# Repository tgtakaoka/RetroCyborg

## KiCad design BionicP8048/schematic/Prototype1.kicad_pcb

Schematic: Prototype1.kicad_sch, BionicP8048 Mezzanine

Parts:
C1: 0.1u; C_Disc_D3.4mm_W2.1mm_P2.50mm
J1: BionicConnector; DIP-48_W7.62mm
U1: MSM80C39RS; DIP-40_W15.24mm
U2: 74HCT126; DIP-14_W7.62mm

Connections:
/P10: J1.2 (P10), U1.12 (DB0)
/P11: J1.3 (P11), U1.13 (DB1)
/P12: J1.4 (P12), U1.14 (DB2)
/P13: J1.5 (P13), U1.15 (DB3)
/P14: J1.6 (P14), U1.16 (DB4)
/P15: J1.7 (P15), U1.17 (DB5)
/P16: J1.8 (P16), U1.18 (DB6)
/P17: J1.9 (P17), U1.19 (DB7)
/P20: J1.47 (P20), U1.21 (A8)
/P21: J1.46 (P21), U1.22 (A9)
/P22: J1.45 (P22), U1.23 (A10)
/P23: J1.44 (P23), U1.24 (A11)
/P40: J1.38 (P40), U1.11 (ALE)
/P41: J1.37 (P41), U1.9 (~PSEN)
/P42: J1.36 (P42), U1.6 (~INT)
/P44: J1.34 (P44), U1.1 (T0)
/P45: J1.33 (P45), U1.39 (T1)
/P46: J1.32 (P46), U2.2 (1A)
/P50: J1.20 (P50), U1.8 (~RD)
/P51: J1.21 (P51), U1.10 (~WR)
/P52: J1.22 (P52), U1.5 (~SS)
/P53: J1.23 (P53), U2.5 (2A)
/P55: J1.28 (P55), U1.25 (~PROG)
GND: C1.2, J1.1 (GND), J1.48 (GND), U1.20 (VSS), U2.7 (GND), U2.9 (3A), U2.10 (3OE), U2.12 (4A), U2.13 (4OE)
unnamed: U1.2 (XTAL1), U2.3 (1Y)
unnamed: U1.4 (~RESET), U2.6 (2Y)
VCC: C1.1, J1.24 (VCC), J1.25 (VCC), U1.7 (EA), U1.26 (VDD), U1.40 (VCC), U2.1 (1OE), U2.4 (2OE), U2.14 (VCC)

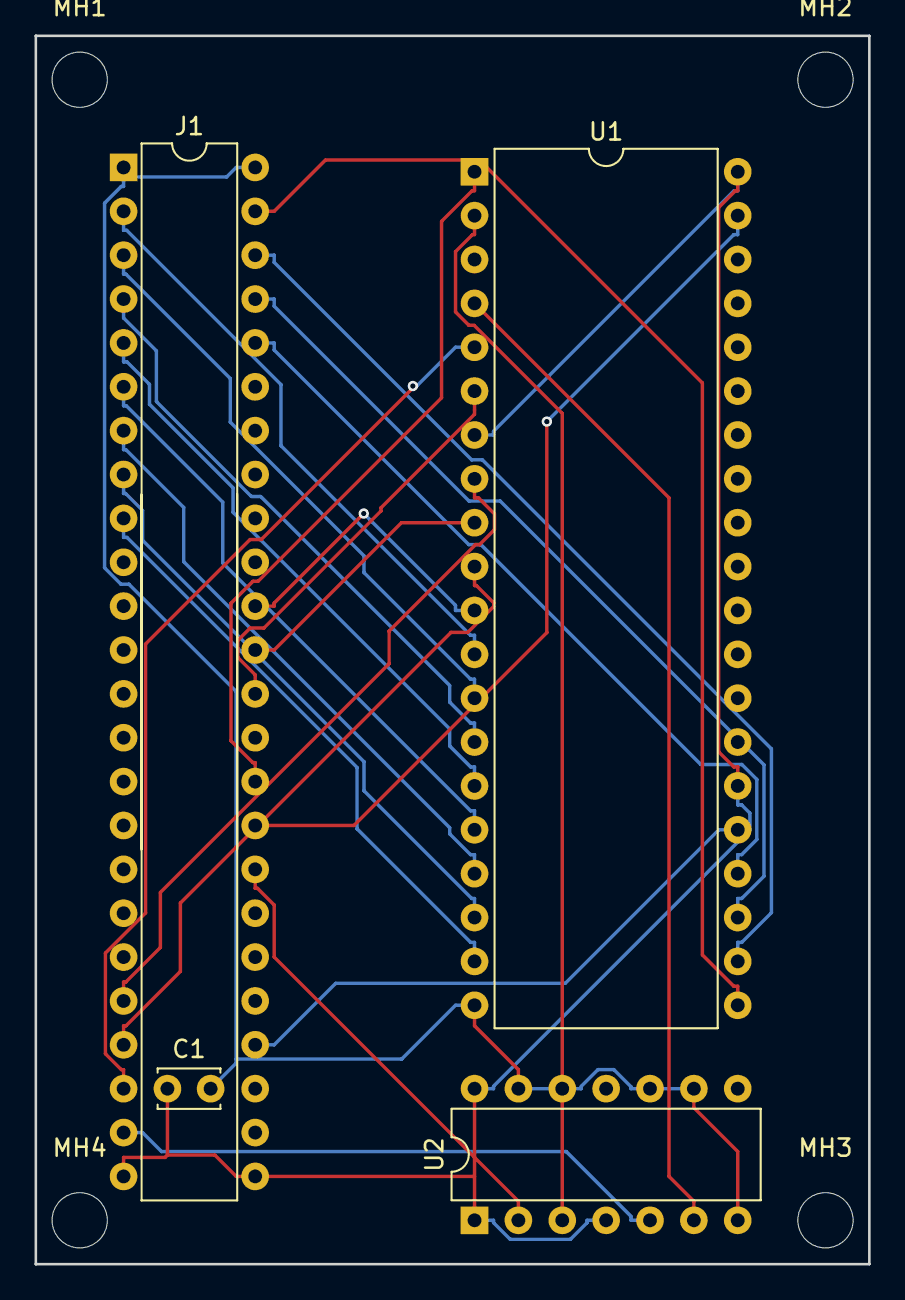
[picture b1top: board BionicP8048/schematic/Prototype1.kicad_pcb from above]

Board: 2 copper layers, 48.3 x 71.1 mm, 8 parts (0 on the bottom side), 27 nets.

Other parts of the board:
MH1, MH2, MH3, MH4: MountingHole_3.2mm_M3

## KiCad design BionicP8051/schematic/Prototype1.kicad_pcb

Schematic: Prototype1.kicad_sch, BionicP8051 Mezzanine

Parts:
C1: 0.1u; C_Disc_D3.4mm_W2.1mm_P2.50mm
J1: BionicConnector; DIP-48_W7.62mm
U1: P80C32; DIP-40_W15.24mm
U2: 74HCT126; DIP-14_W7.62mm

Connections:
/P10: J1.2 (P10), U1.39 (AD0)
/P11: J1.3 (P11), U1.38 (AD1)
/P12: J1.4 (P12), U1.37 (AD2)
/P13: J1.5 (P13), U1.36 (AD3)
/P14: J1.6 (P14), U1.35 (AD4)
/P15: J1.7 (P15), U1.33 (AD5)
/P16: J1.8 (P16), U1.34 (AD6)
/P17: J1.9 (P17), U1.32 (AD7)
/P20: J1.47 (P20), U1.21 (A8)
/P21: J1.46 (P21), U1.22 (A9)
/P22: J1.45 (P22), U1.23 (A10)
/P23: J1.44 (P23), U1.24 (A11)
/P24: J1.43 (P24), U1.25 (A12)
/P25: J1.42 (P25), U1.26 (A13)
/P26: J1.41 (P26), U1.27 (A14)
/P27: J1.40 (P27), U1.28 (A15)
/P40: J1.38 (P40), U1.30 (ALE)
/P41: J1.37 (P41), U1.29 (~PSEN)
/P42: J1.36 (P42), U1.13 (~INT1)
/P43: J1.35 (P43), U1.12 (~INT0)
/P44: J1.34 (P44), U1.11 (TxD/P3.1)
/P45: J1.33 (P45), U1.10 (RxD/P3.0)
/P46: J1.32 (P46), U2.2 (1A)
/P50: J1.20 (P50), U1.17 (~RD)
/P51: J1.21 (P51), U1.16 (~WR)
/P53: J1.23 (P53), U2.5 (2A)
GND: C1.2, J1.1 (GND), J1.48 (GND), U1.20 (VSS), U2.7 (GND), U2.9 (3A), U2.10 (3OE), U2.12 (4A), U2.13 (4OE)
unnamed: U1.9 (RESET), U2.6 (2Y)
unnamed: U1.19 (XTAL1), U2.3 (1Y)
VCC: C1.1, J1.24 (VCC), J1.25 (VCC), U1.31 (~EA), U1.40 (VCC), U2.1 (1OE), U2.4 (2OE), U2.14 (VCC)

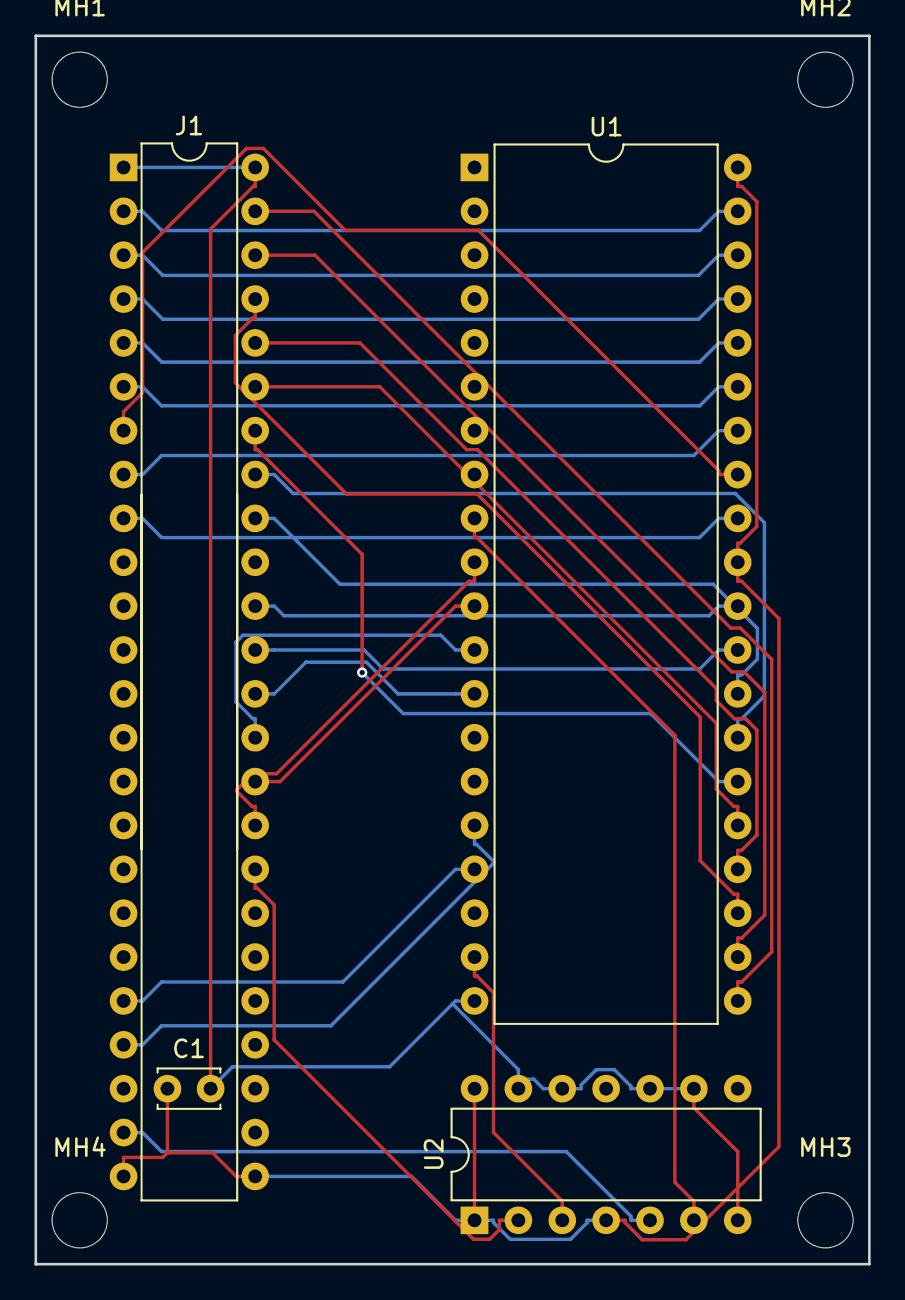
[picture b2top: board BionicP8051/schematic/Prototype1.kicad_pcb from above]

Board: 2 copper layers, 48.3 x 71.1 mm, 8 parts (0 on the bottom side), 30 nets.

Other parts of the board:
MH1, MH2, MH3, MH4: MountingHole_3.2mm_M3

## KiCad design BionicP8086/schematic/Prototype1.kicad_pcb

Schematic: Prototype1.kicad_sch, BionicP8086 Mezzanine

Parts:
C1: 0.1u; C_Disc_D3.4mm_W2.1mm_P2.50mm
J1: BionicConnector; DIP-48_W7.62mm
U1: P80C86A; DIP-40_W15.24mm
U2: 74HCT126; DIP-14_W7.62mm

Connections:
/P10: J1.2 (P10), U1.16 (AD0)
/P11: J1.3 (P11), U1.15 (AD1)
/P12: J1.4 (P12), U1.14 (AD2)
/P13: J1.5 (P13), U1.13 (AD3)
/P14: J1.6 (P14), U1.12 (AD4)
/P15: J1.7 (P15), U1.11 (AD5)
/P16: J1.8 (P16), U1.10 (AD6)
/P17: J1.9 (P17), U1.9 (AD7)
/P20: J1.47 (P20), U1.8 (AD8)
/P21: J1.46 (P21), U1.7 (AD9)
/P22: J1.45 (P22), U1.6 (AD10)
/P23: J1.44 (P23), U1.5 (AD11)
/P24: J1.43 (P24), U1.4 (AD12)
/P25: J1.42 (P25), U1.3 (AD13)
/P26: J1.41 (P26), U1.2 (AD14)
/P27: J1.40 (P27), U1.39 (AD15)
/P30: J1.11 (P30), U1.38 (A16)
/P31: J1.12 (P31), U1.37 (A17)
/P32: J1.13 (P32), U1.36 (A18)
/P33: J1.14 (P33), U1.35 (A19)
/P34: J1.15 (P34), U1.34 (~BHE)
/P35: J1.16 (P35), U1.27 (DT/~R)
/P36: J1.17 (P36), U1.30 (HLDA)
/P37: J1.18 (P37), U1.31 (HOLD)
/P40: J1.38 (P40), U1.25 (ALE)
/P42: J1.36 (P42), U1.18 (INTR)
/P43: J1.35 (P43), U1.17 (NMI)
/P44: J1.34 (P44), U1.26 (~DEN)
/P46: J1.32 (P46), U2.2 (1A)
/P47: J1.31 (P47), U1.33 (MN/~MX)
/P50: J1.20 (P50), U1.32 (~RD)
/P51: J1.21 (P51), U1.29 (~WR)
/P52: J1.22 (P52), U1.22 (READY)
/P53: J1.23 (P53), U1.21 (RESET)
/P54: J1.29 (P54), U1.24 (~INTA)
/P55: J1.28 (P55), U1.28 (M/~IO)
GND: C1.2, J1.1 (GND), J1.48 (GND), U1.1 (GND), U1.20 (GND), U2.5 (2A), U2.7 (GND), U2.9 (3A), U2.10 (3OE), U2.12 (4A), U2.13 (4OE)
unnamed: U1.19 (CLK), U2.3 (1Y)
VCC: C1.1, J1.24 (VCC), J1.25 (VCC), U1.23 (~TEST), U1.40 (VCC), U2.1 (1OE), U2.4 (2OE), U2.14 (VCC)

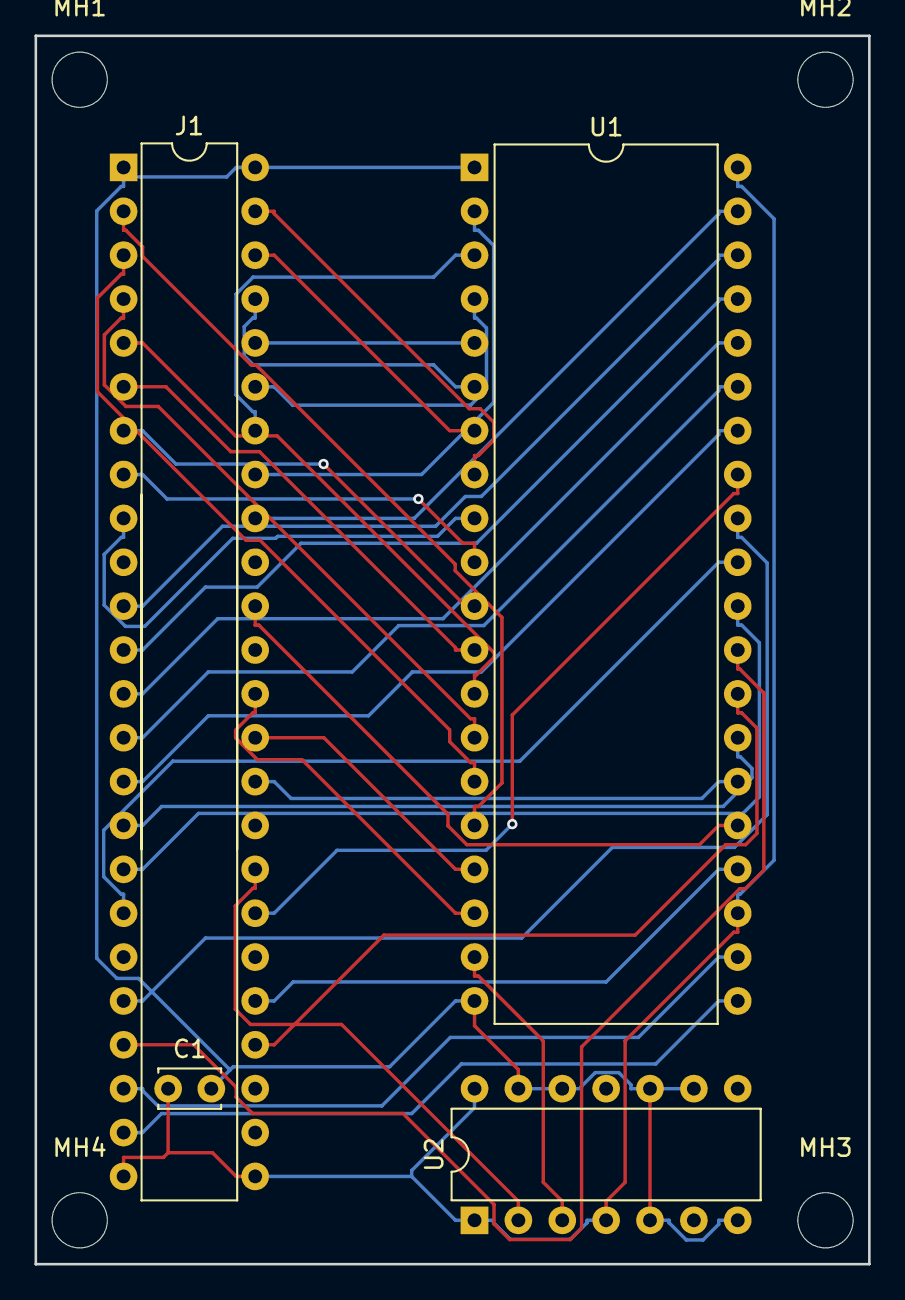
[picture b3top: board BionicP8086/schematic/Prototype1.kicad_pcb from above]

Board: 2 copper layers, 48.3 x 71.1 mm, 8 parts (0 on the bottom side), 39 nets.

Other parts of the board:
MH1, MH2, MH3, MH4: MountingHole_3.2mm_M3

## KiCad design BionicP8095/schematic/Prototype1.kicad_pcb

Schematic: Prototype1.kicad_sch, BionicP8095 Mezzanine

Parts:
C1: 0.1u; C_Disc_D3.4mm_W2.1mm_P2.50mm
J1: BionicConnector; DIP-48_W7.62mm
U1: P8095BH; DIP-48_W15.24mm
U2: 74HCT126; DIP-14_W7.62mm

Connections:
/P10: J1.2 (P10), U1.32 (AD0)
/P11: J1.3 (P11), U1.31 (AD1)
/P12: J1.4 (P12), U1.30 (AD2)
/P13: J1.5 (P13), U1.29 (AD3)
/P14: J1.6 (P14), U1.28 (AD4)
/P15: J1.7 (P15), U1.27 (AD5)
/P16: J1.8 (P16), U1.26 (AD6)
/P17: J1.9 (P17), U1.25 (AD7)
/P20: J1.47 (P20), U1.24 (AD8)
/P21: J1.46 (P21), U1.23 (AD9)
/P22: J1.45 (P22), U1.22 (AD10)
/P23: J1.44 (P23), U1.21 (AD11)
/P24: J1.43 (P24), U1.20 (AD12)
/P25: J1.42 (P25), U1.19 (AD13)
/P26: J1.41 (P26), U1.18 (AD14)
/P27: J1.40 (P27), U1.17 (AD15)
/P40: J1.38 (P40), U1.34 (ALE)
/P42: J1.36 (P42), U1.47 (EXTINT)
/P44: J1.34 (P44), U1.2 (TxD/P2.0)
/P45: J1.33 (P45), U1.1 (RxD/P2.1)
/P46: J1.32 (P46), U2.2 (1A)
/P50: J1.20 (P50), U1.33 (~RD)
/P51: J1.21 (P51), U1.14 (~WR)
/P52: J1.22 (P52), U1.16 (READY)
/P53: J1.23 (P53), U2.5 (2A)
/P55: J1.28 (P55), U1.15 (~HBE)
GND: C1.2, J1.1 (GND), J1.48 (GND), U1.11 (Vss), U1.37 (Vss), U1.39 (~EA), U1.44 (ANGND), U2.7 (GND), U2.9 (3A), U2.10 (3OE), U2.12 (4A), U2.13 (4OE)
unnamed: U1.36 (XTAL1), U2.3 (1Y)
unnamed: U1.48 (~RESET), U2.6 (2Y)
VCC: C1.1, J1.24 (VCC), J1.25 (VCC), U1.38 (Vcc), U1.45 (Vref), U1.46 (Vpd), U2.1 (1OE), U2.4 (2OE), U2.14 (VCC)

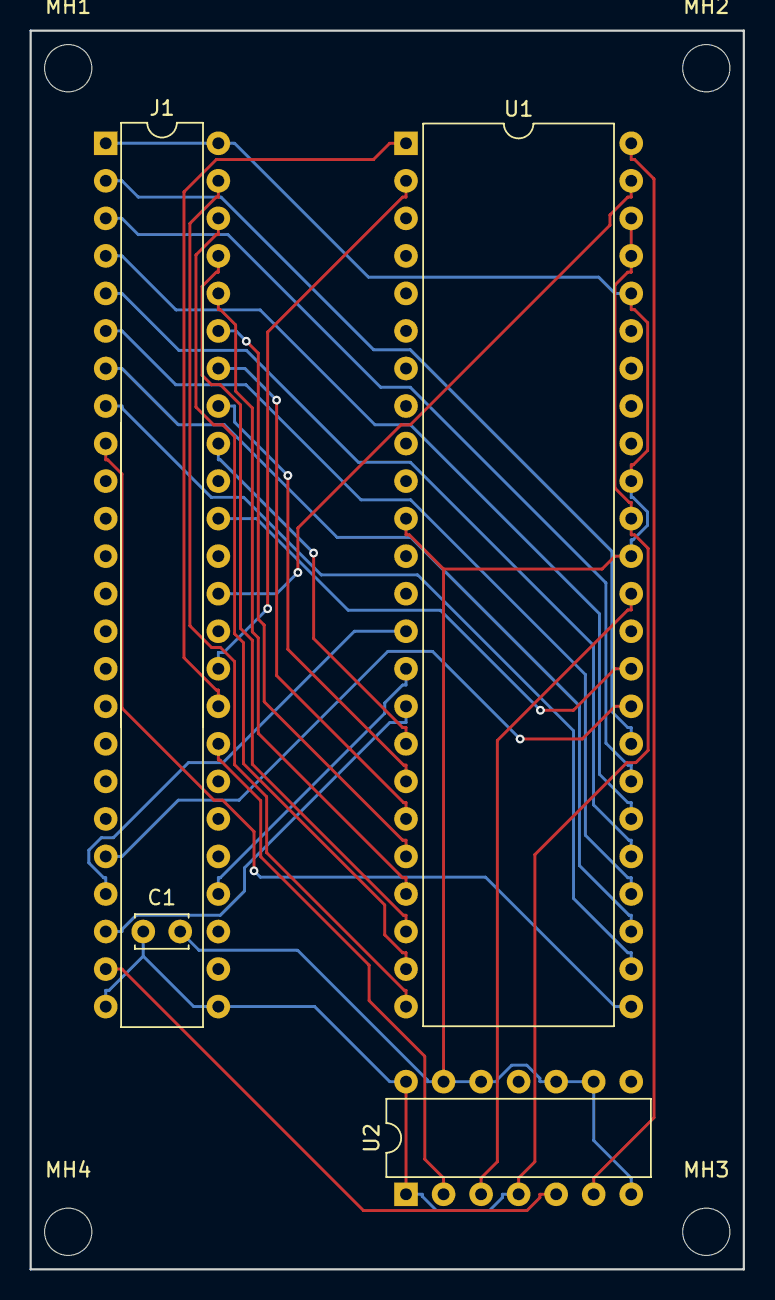
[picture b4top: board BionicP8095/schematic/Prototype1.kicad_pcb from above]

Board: 2 copper layers, 48.3 x 83.8 mm, 8 parts (0 on the bottom side), 30 nets.

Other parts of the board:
MH1, MH2, MH3, MH4: MountingHole_3.2mm_M3

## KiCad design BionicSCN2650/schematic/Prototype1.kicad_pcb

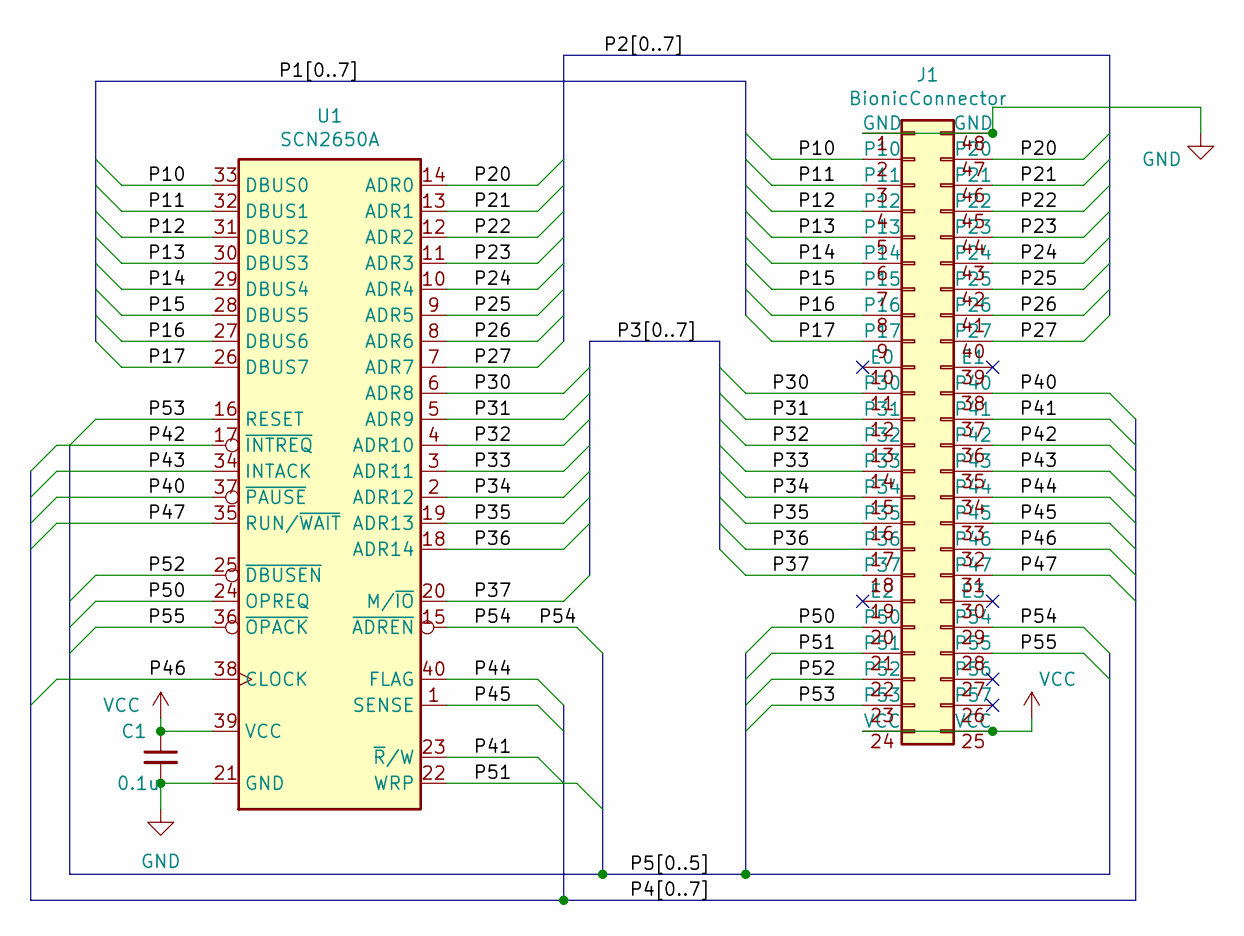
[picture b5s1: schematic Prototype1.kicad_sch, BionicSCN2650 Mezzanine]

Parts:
C1: 0.1u; C_Disc_D3.4mm_W2.1mm_P2.50mm
J1: BionicConnector; DIP-48_W7.62mm
U1: SCN2650A; DIP-40_W15.24mm

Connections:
/P10: J1.2 (P10), U1.33 (DBUS0)
/P11: J1.3 (P11), U1.32 (DBUS1)
/P12: J1.4 (P12), U1.31 (DBUS2)
/P13: J1.5 (P13), U1.30 (DBUS3)
/P14: J1.6 (P14), U1.29 (DBUS4)
/P15: J1.7 (P15), U1.28 (DBUS5)
/P16: J1.8 (P16), U1.27 (DBUS6)
/P17: J1.9 (P17), U1.26 (DBUS7)
/P20: J1.47 (P20), U1.14 (ADR0)
/P21: J1.46 (P21), U1.13 (ADR1)
/P22: J1.45 (P22), U1.12 (ADR2)
/P23: J1.44 (P23), U1.11 (ADR3)
/P24: J1.43 (P24), U1.10 (ADR4)
/P25: J1.42 (P25), U1.9 (ADR5)
/P26: J1.41 (P26), U1.8 (ADR6)
/P27: J1.40 (P27), U1.7 (ADR7)
/P30: J1.11 (P30), U1.6 (ADR8)
/P31: J1.12 (P31), U1.5 (ADR9)
/P32: J1.13 (P32), U1.4 (ADR10)
/P33: J1.14 (P33), U1.3 (ADR11)
/P34: J1.15 (P34), U1.2 (ADR12)
/P35: J1.16 (P35), U1.19 (ADR13)
/P36: J1.17 (P36), U1.18 (ADR14)
/P37: J1.18 (P37), U1.20 (M/~IO)
/P40: J1.38 (P40), U1.37 (~PAUSE)
/P41: J1.37 (P41), U1.23 (~R/W)
/P42: J1.36 (P42), U1.17 (~INTREQ)
/P43: J1.35 (P43), U1.34 (INTACK)
/P44: J1.34 (P44), U1.40 (FLAG)
/P45: J1.33 (P45), U1.1 (SENSE)
/P46: J1.32 (P46), U1.38 (CLOCK)
/P47: J1.31 (P47), U1.35 (RUN/~WAIT)
/P50: J1.20 (P50), U1.24 (OPREQ)
/P51: J1.21 (P51), U1.22 (WRP)
/P52: J1.22 (P52), U1.25 (~DBUSEN)
/P53: J1.23 (P53), U1.16 (RESET)
/P54: J1.29 (P54), U1.15 (~ADREN)
/P55: J1.28 (P55), U1.36 (~OPACK)
GND: C1.2, J1.1 (GND), J1.48 (GND), U1.21 (GND)
VCC: C1.1, J1.24 (VCC), J1.25 (VCC), U1.39 (VCC)

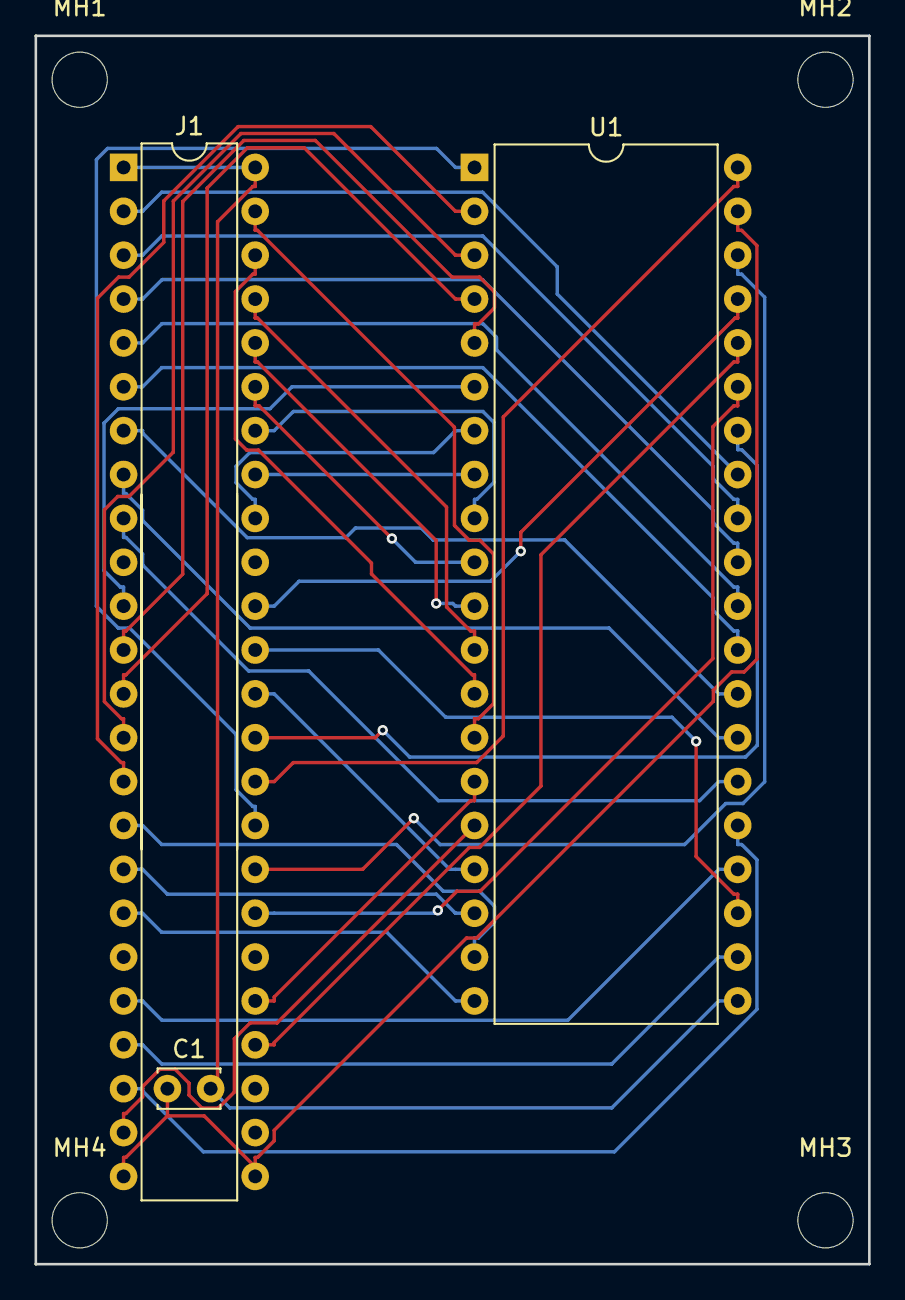
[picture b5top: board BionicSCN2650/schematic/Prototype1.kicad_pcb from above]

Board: 2 copper layers, 48.3 x 71.1 mm, 7 parts (0 on the bottom side), 40 nets.

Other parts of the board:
MH1, MH2, MH3, MH4: MountingHole_3.2mm_M3

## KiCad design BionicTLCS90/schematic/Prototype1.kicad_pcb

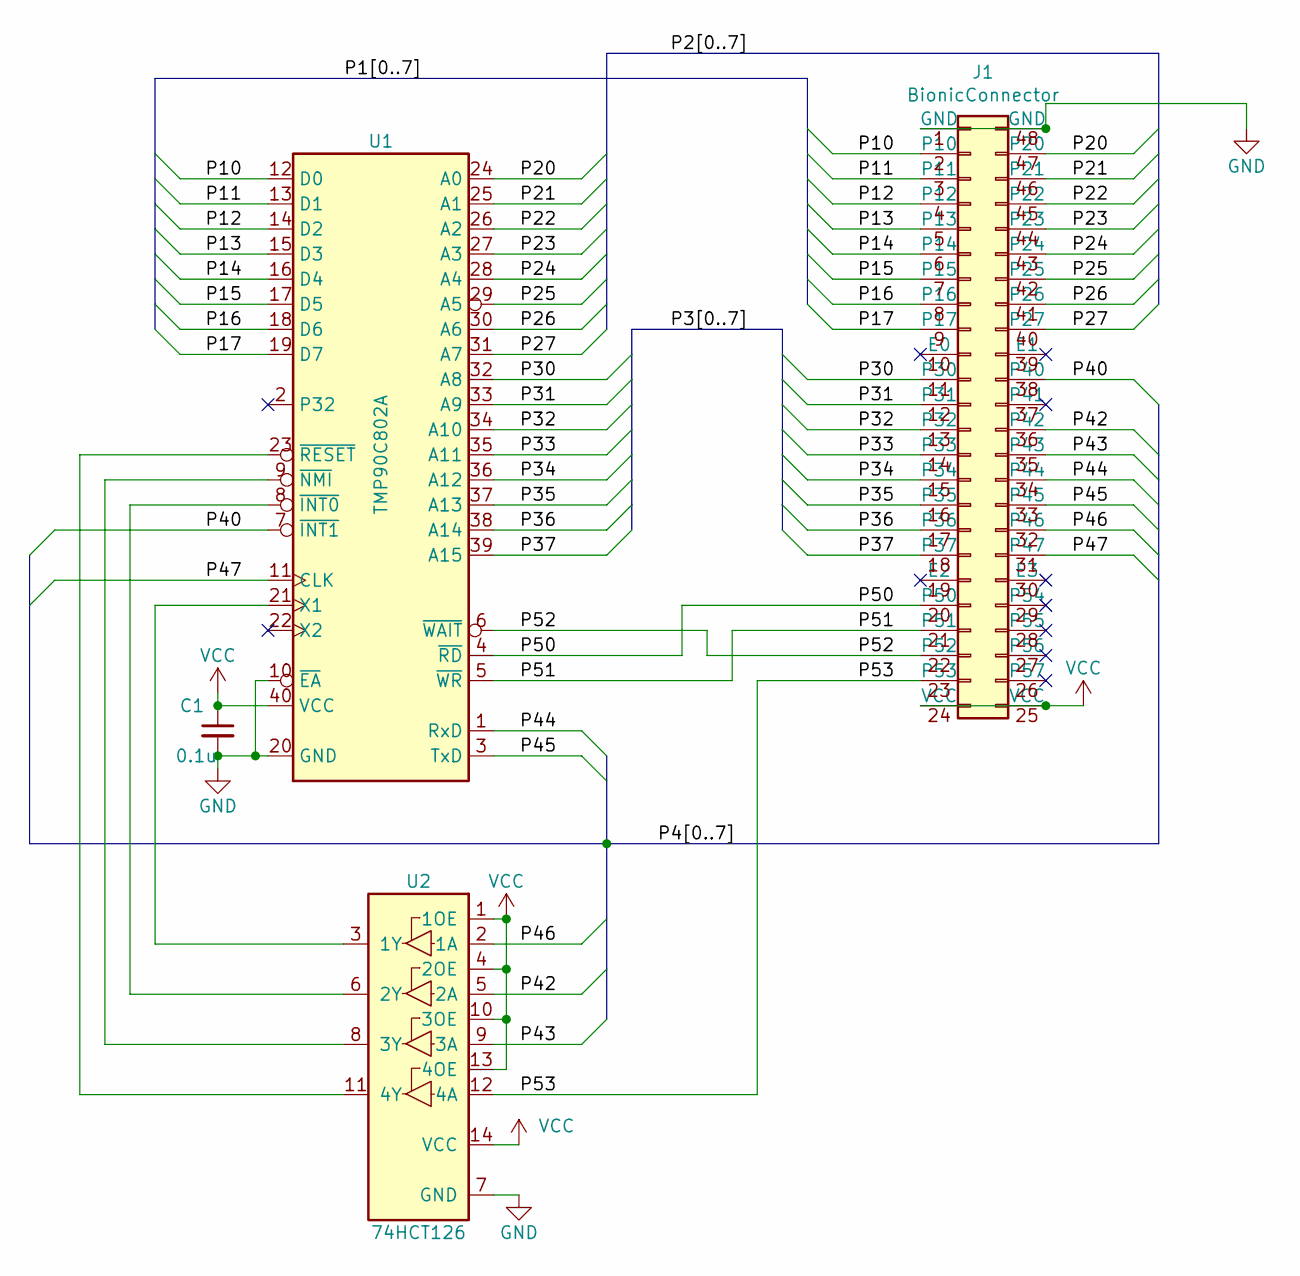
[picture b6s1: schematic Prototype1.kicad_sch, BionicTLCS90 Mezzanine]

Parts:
C1: 0.1u; C_Disc_D3.4mm_W2.1mm_P2.50mm
J1: BionicConnector; DIP-48_W7.62mm
U1: TMP90C802A; DIP-40_W15.24mm
U2: 74HCT126; DIP-14_W7.62mm

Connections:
/P10: J1.2 (P10), U1.12 (D0)
/P11: J1.3 (P11), U1.13 (D1)
/P12: J1.4 (P12), U1.14 (D2)
/P13: J1.5 (P13), U1.15 (D3)
/P14: J1.6 (P14), U1.16 (D4)
/P15: J1.7 (P15), U1.17 (D5)
/P16: J1.8 (P16), U1.18 (D6)
/P17: J1.9 (P17), U1.19 (D7)
/P20: J1.47 (P20), U1.24 (A0)
/P21: J1.46 (P21), U1.25 (A1)
/P22: J1.45 (P22), U1.26 (A2)
/P23: J1.44 (P23), U1.27 (A3)
/P24: J1.43 (P24), U1.28 (A4)
/P25: J1.42 (P25), U1.29 (A5)
/P26: J1.41 (P26), U1.30 (A6)
/P27: J1.40 (P27), U1.31 (A7)
/P30: J1.11 (P30), U1.32 (A8)
/P31: J1.12 (P31), U1.33 (A9)
/P32: J1.13 (P32), U1.34 (A10)
/P33: J1.14 (P33), U1.35 (A11)
/P34: J1.15 (P34), U1.36 (A12)
/P35: J1.16 (P35), U1.37 (A13)
/P36: J1.17 (P36), U1.38 (A14)
/P37: J1.18 (P37), U1.39 (A15)
/P40: J1.38 (P40), U1.7 (~INT1)
/P42: J1.36 (P42), U2.5 (2A)
/P43: J1.35 (P43), U2.9 (3A)
/P44: J1.34 (P44), U1.1 (RxD)
/P45: J1.33 (P45), U1.3 (TxD)
/P46: J1.32 (P46), U2.2 (1A)
/P47: J1.31 (P47), U1.11 (CLK)
/P50: J1.20 (P50), U1.4 (~RD)
/P51: J1.21 (P51), U1.5 (~WR)
/P52: J1.22 (P52), U1.6 (~WAIT)
/P53: J1.23 (P53), U2.12 (4A)
GND: C1.2, J1.1 (GND), J1.48 (GND), U1.10 (~EA), U1.20 (GND), U2.7 (GND)
unnamed: U1.21 (X1), U2.3 (1Y)
unnamed: U1.8 (~INT0), U2.6 (2Y)
unnamed: U1.9 (~NMI), U2.8 (3Y)
unnamed: U1.23 (~RESET), U2.11 (4Y)
VCC: C1.1, J1.24 (VCC), J1.25 (VCC), U1.40 (VCC), U2.1 (1OE), U2.4 (2OE), U2.10 (3OE), U2.13 (4OE), U2.14 (VCC)

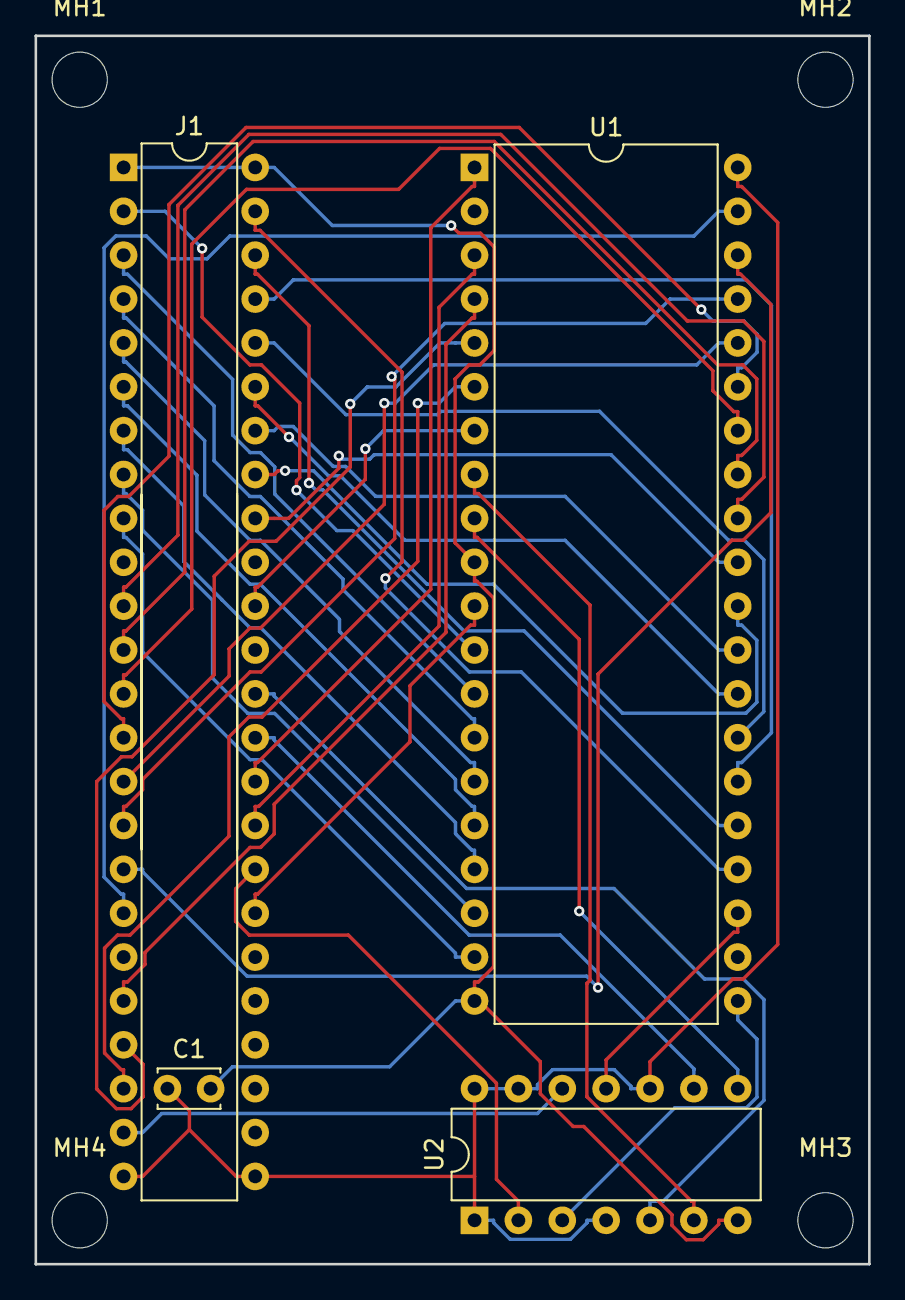
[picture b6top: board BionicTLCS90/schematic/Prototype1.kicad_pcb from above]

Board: 2 copper layers, 48.3 x 71.1 mm, 8 parts (0 on the bottom side), 41 nets.

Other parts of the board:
MH1, MH2, MH3, MH4: MountingHole_3.2mm_M3
